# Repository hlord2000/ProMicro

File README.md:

# Pro Micro Project Template

This KiCAD Template simplifies initial setup for ProMicro PCB designs.

To begin, clone this repository to your KICAD_USER_TEMPLATE_DIR as found under "Preferences > Configure Paths..."

Next, use "File > New Project from Template..." or "Ctrl+T" and select "User Templates." Select the template and begin!

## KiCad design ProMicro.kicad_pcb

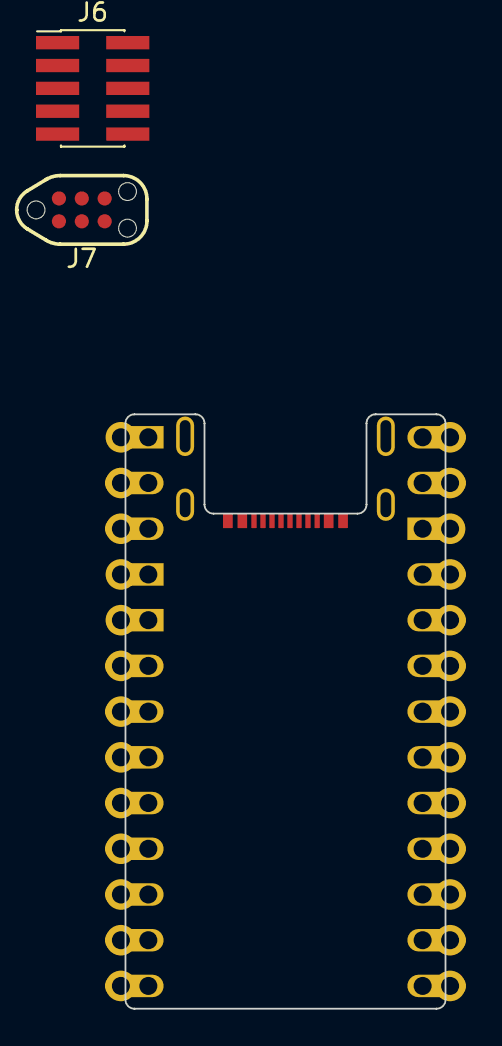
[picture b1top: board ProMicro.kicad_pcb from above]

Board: 2 copper layers, 17.8 x 33.0 mm, 4 parts (0 on the bottom side), 8 nets, no tracks yet.

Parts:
J3: USB_C_Receptacle_USB2.0_16P; USB_C_Receptacle_Jing_918-418K2024S40000
J6: Conn_ARM_JTAG_SWD_10; PinHeader_2x05_P1.27mm_Vertical_SMD
J7: TC2030_SWD; CON_TC2030_outlined
J102: Conn_02x13_Top_Bottom; Connector_Pro_Micro_Castellated

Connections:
/D+: J3.A6 (D+), J3.B6 (D+)
/D-: J3.A7 (D-), J3.B7 (D-)
/SWCLK: J6.4 (SWCLK/TCK), J7.4 (SWCLK)
/SWDIO: J6.2 (SWDIO/TMS), J7.2 (SWDIO)
/SWO: J6.6 (SWO/TDO), J7.6 (SWO)
/~RESET: J6.10 (~RESET), J7.3 (~RST)
GND: J3.A1 (GND), J3.S1 (SHIELD), J6.3 (GND), J6.5 (GND), J6.9 (GNDDetect), J7.5 (GND), J102.1, J102.4, J102.16
VCC: J6.1 (VTref), J7.1 (VCC)
